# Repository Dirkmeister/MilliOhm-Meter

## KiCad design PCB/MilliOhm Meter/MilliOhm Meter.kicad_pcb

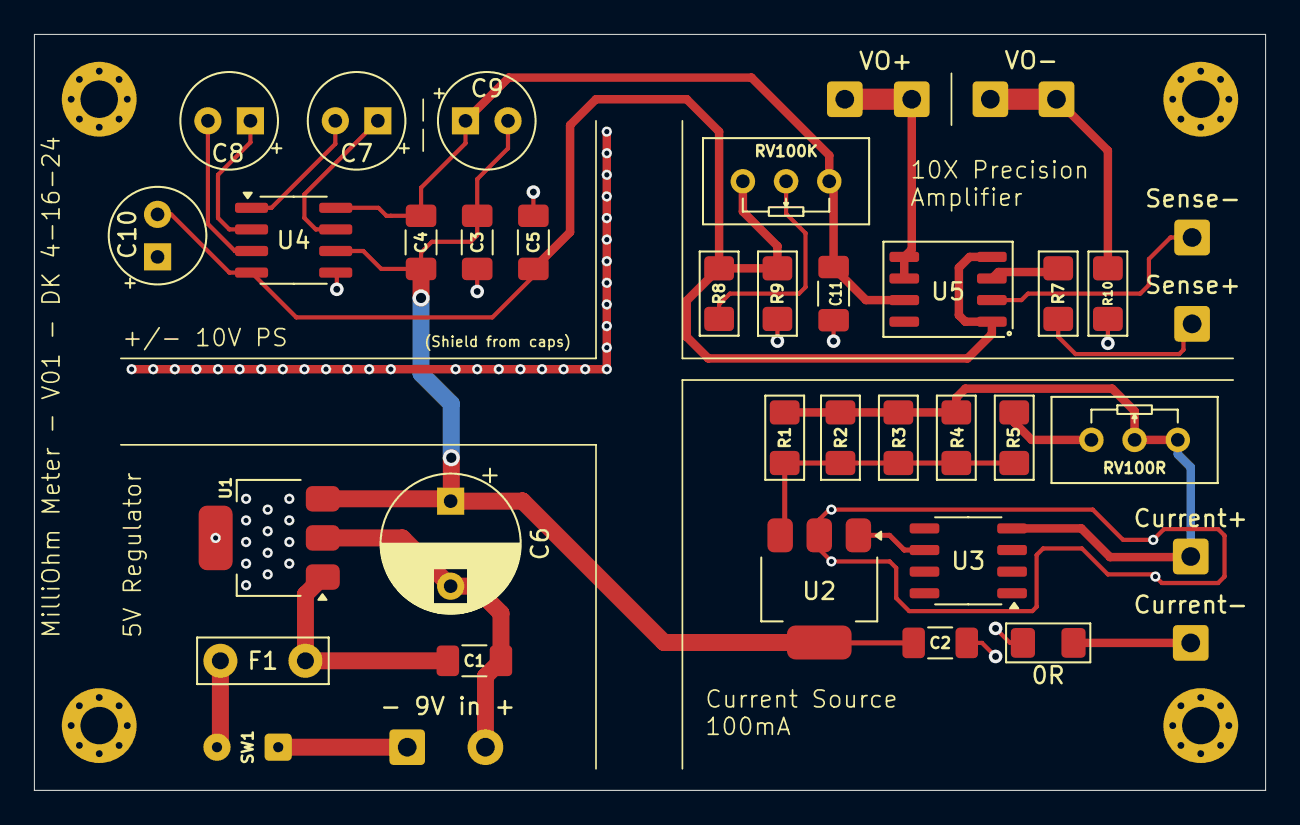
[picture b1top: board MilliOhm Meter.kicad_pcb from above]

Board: 2 copper layers, 72.4 x 44.5 mm, 43 parts (0 on the bottom side), 22 nets.

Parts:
0R: 0R; R_1206_3216Metric_Pad1.42x1.75mm_HandSolder
C1, C2, C3, C4, C5, C11: 0.1uF; C_1206_3216Metric_Pad1.33x1.80mm_HandSolder
C6: 220uF; CP_Radial_D8.0mm_P5.00mm
C7, C8, C9, C10: 22uF; CP_Radial_Tantal_D5.5mm_P2.50mm
Current+: Conn_01x01_Pin; SolderWire-0.5sqmm_1x01_D0.9mm_OD2.1mm
Current-: Conn_01x01_Pin; SolderWire-0.5sqmm_1x01_D0.9mm_OD2.1mm
F1: PTC 250mA; C_Disc_D7.5mm_W2.5mm_P5.00mm
H1, H2, H3, H4: M2; MountingHole_2.2mm_M2_Pad_Via
J1: - 9V in +; SolderWire-0.5sqmm_1x02_P4.6mm_D0.9mm_OD2.1mm
J6, J7: Conn_01x01_Pin; SolderWire-0.5sqmm_1x01_D0.9mm_OD2.1mm
R1, R2, R3, R4: 56R2; R_1206_3216Metric_Pad1.42x1.75mm_HandSolder
R5: 63R4; R_1206_3216Metric_Pad1.42x1.75mm_HandSolder
R7: 10r; R_1206_3216Metric_Pad1.42x1.75mm_HandSolder
R8: 499K; R_1206_3216Metric_Pad1.42x1.75mm_HandSolder
R9: 100R; R_1206_3216Metric_Pad1.42x1.75mm_HandSolder
R10: 0R; R_1206_3216Metric_Pad1.42x1.75mm_HandSolder
RV100K: 100K; Potentiometer_Bourns_3296W_Vertical
RV100R: 100R; Potentiometer_Bourns_3296W_Vertical
SW1: SW_SPST; SolderWire-0.1sqmm_1x02_P3.6mm_D0.4mm_OD1mm
Sense+: Conn_01x01_Pin; SolderWire-0.5sqmm_1x01_D0.9mm_OD2.1mm
Sense-: Conn_01x01_Pin; SolderWire-0.5sqmm_1x01_D0.9mm_OD2.1mm
U1: SOT-223
U2: LT3092xST; SOT-223-3_TabPin2
U3: LT1634-1.25; SO-8_3.9x4.9mm_P1.27mm
U4: MAX680CPA+; SOIC-8_3.9x4.9mm_P1.27mm
U5: INA106U; SO-8_3.9x4.9mm_P1.27mm
VO+: Conn_01x01_Pin; SolderWire-0.5sqmm_1x01_D0.9mm_OD2.1mm
VO-: Conn_01x01_Pin; SolderWire-0.5sqmm_1x01_D0.9mm_OD2.1mm

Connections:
+5V: C2.1, C3.2, C4.1, C6.1, C9.2, U1.3 (VO), U2.2, U4.6 (VCC)
/+10V: C4.2, C9.1, C11.1, RV100K.3, U4.8 (V+), U5.7 (V+)
/-10V: C5.1, C10.2, R8.2, R9.1, RV100K.1, U4.4 (V-), U5.1 (REF), U5.4 (V-)
/Current+: Current+.1, R1.2, R2.2, R3.2, R4.2, RV100R.1, RV100R.2, U3.4 (A)
/Current-: 0R.2, Current-.1
/Sense+: R7.1, Sense+.1
/Sense-: Sense-.1, U5.2 (IN-)
/VO+: J6.1, U5.5 (SENSE), U5.6 (OUT), VO+.1
/VO-: J7.1, R10.2, VO-.1
GND: 0R.1, C1.2, C2.2, C3.1, C5.2, C6.2, C10.1, C11.2, J1.2, R9.2, R10.1, U1.2 (GND), U1.4 (GND), U4.5 (GND)
unnamed: J1.1, SW1.1 (A)
unnamed: R1.1, R2.1, R3.1, R4.1, R5.1, U2.3
unnamed: R5.2, RV100R.3
unnamed: R8.1, RV100K.2
unnamed: F1.1, SW1.2 (B)
unnamed: C1.1, F1.2, U1.1 (VI)
unnamed: U2.1, U3.6 (K)
unnamed: C7.1, U4.7 (C1+)
unnamed: C7.2, U4.1 (C1-)
unnamed: C8.1, U4.2 (C2+)
unnamed: C8.2, U4.3 (C2-)
unnamed: R7.2, U5.3 (IN+)

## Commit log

2024-04-11 Schematic Complete
    Milliohm schematic complete
2024-04-11 DC charge pump layout
    PCB update
2024-04-17 PCB Progress
    Component layout complete, board outline complete, routing in progress.
2024-04-18 First Draft PCB done
    Revision 1 of the PCB is done, next step will be the probe design
